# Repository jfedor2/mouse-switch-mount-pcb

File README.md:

# Mouse switch mount PCB

This repository contains design files for a small PCB that can be used to attach mouse button switches like Omron D2F or Kailh GM to a case using M2 screws.

The Gerber zip file can be used to order the board from JLCPCB (and probably many other places).

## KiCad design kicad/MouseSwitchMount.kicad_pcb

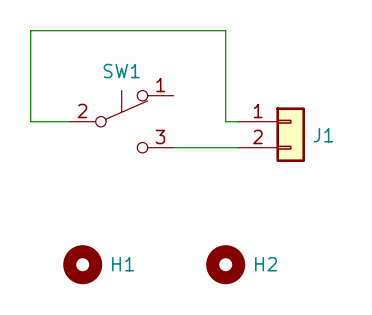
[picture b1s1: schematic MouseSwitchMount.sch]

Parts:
H1, H2: MountingHole; MountingHole_2.2mm_M2
J1: Conn_01x02; PinHeader_1x02_P2.54mm_Vertical
SW1: SW_Push_SPDT; MouseSwitch

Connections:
unnamed: J1.1, SW1.2 (B)
unnamed: J1.2, SW1.3 (C)

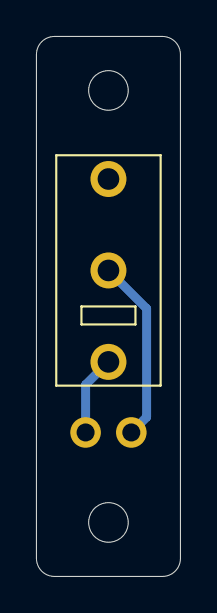
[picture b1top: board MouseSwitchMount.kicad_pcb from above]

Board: 2 copper layers, 8.0 x 30.0 mm, 4 parts (0 on the bottom side), 2 nets.
